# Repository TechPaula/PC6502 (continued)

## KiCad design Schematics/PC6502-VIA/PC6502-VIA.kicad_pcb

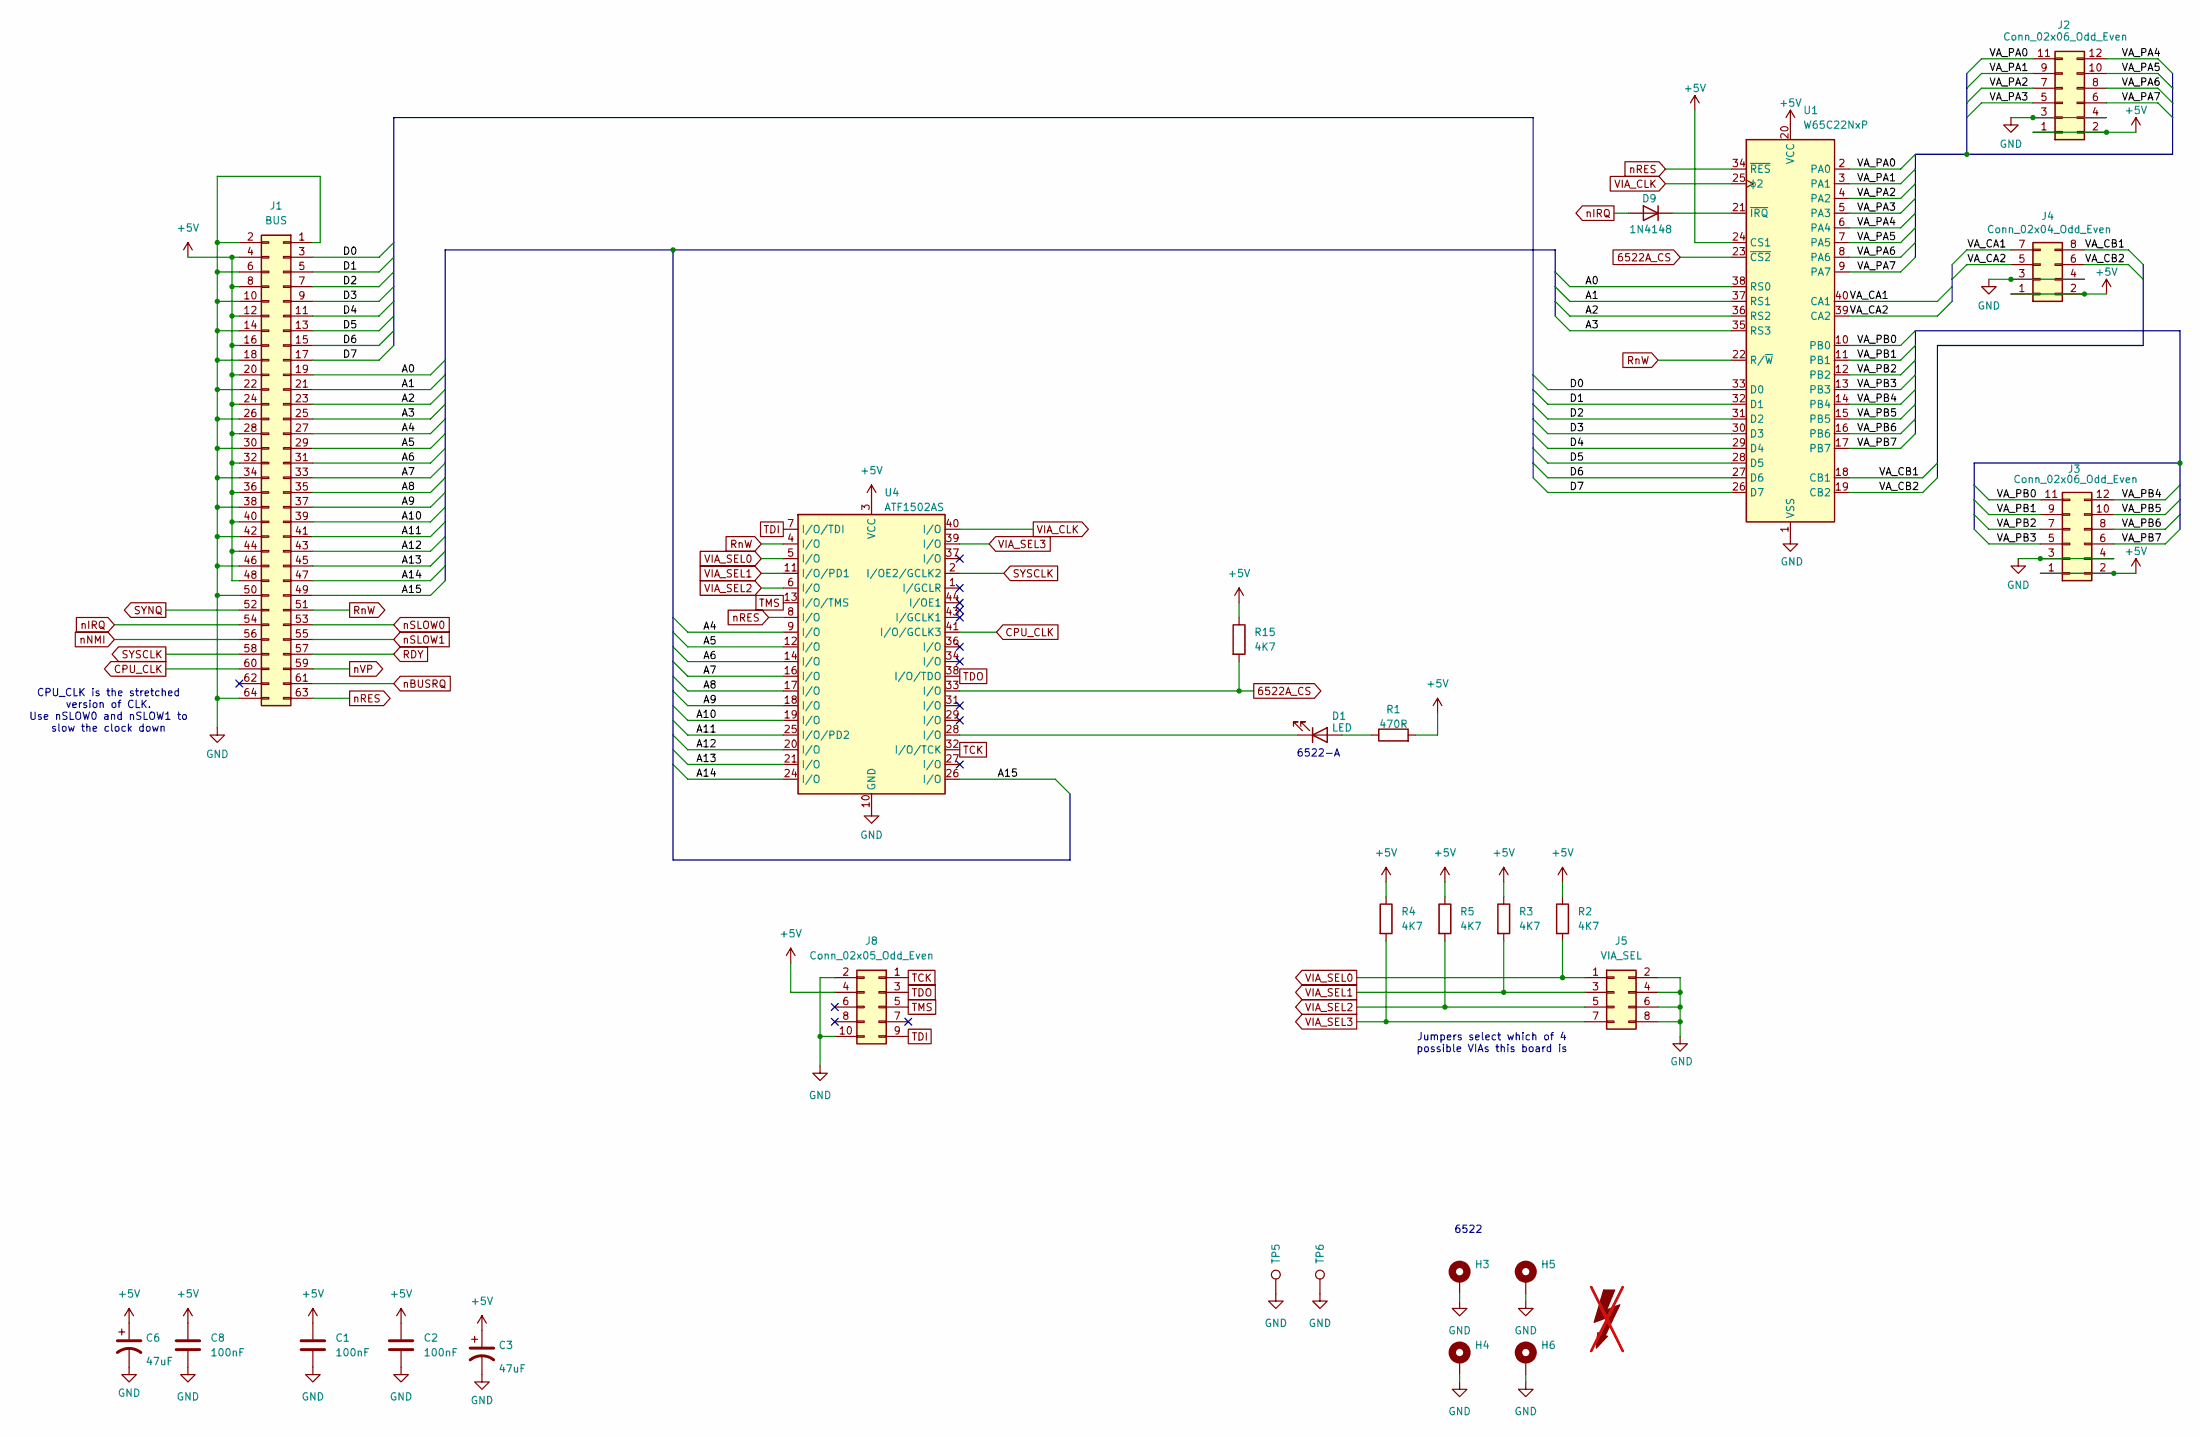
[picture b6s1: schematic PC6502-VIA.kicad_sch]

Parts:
C1, C2, C8: 100nF; C_0805_2012Metric
C3, C6: 47uF; C_1206_3216Metric; LCSC C96123
D1: LED; LTL4221NHBP
D9: 1N4148; D_DO-35_SOD27_P7.62mm_Horizontal
FOX1: SYM_Flash_Large; Fox_avatar_18mm; LCSC DNF; not fitted
H3, H4, H5, H6: MountingHole_Pad; MountingHole_3.2mm_M3_Pad_TopBottom; LCSC DNF
J1: BUS; PinSocket_2x32_P2.54mm_Vertical; LCSC DNF
J2, J3: Conn_02x06_Odd_Even; PinSocket_2x06_P2.54mm_Horizontal
J4: Conn_02x04_Odd_Even; PinSocket_2x04_P2.54mm_Horizontal
J5: VIA_SEL; PinHeader_2x04_P2.54mm_Horizontal
J8: Conn_02x05_Odd_Even; PinHeader_2x05_P2.54mm_Vertical
R1: 470R; R_0603_1608Metric_Pad0.98x0.95mm_HandSolder
R2, R3, R4, R5, R15: 4K7; R_0603_1608Metric_Pad0.98x0.95mm_HandSolder
TP5, TP6: TestPoint; TestPoint_Loop_D1.80mm_Drill1.0mm_Beaded
U1: W65C22NxP; DIP-40_W15.24mm
U4: ATF1502AS; PLCC-44_THT-Socket

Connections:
6522A_CS: R15.2, U1.23 (~CS2), U4.33 (I/O)
+5V: C1.1, C2.1, C3.1, C6.1, C8.1, J1.4, J1.8, J1.12, J1.16, J1.20, J1.24, J1.28, J1.32, J1.36, J1.40, J1.44, J1.48, J2.1, J2.2, J3.1, J3.2, J4.1, J4.2, J8.4, R1.2, R2.1, R3.1, R4.1, R5.1, R15.1, U1.20 (VCC), U1.24 (CS1), U4.3 (VCC), U4.15 (VCC), U4.23 (VCC), U4.35 (VCC)
/A0: J1.19, U1.38 (RS0)
/A1: J1.21, U1.37 (RS1)
/A2: J1.23, U1.36 (RS2)
/A3: J1.25, U1.35 (RS3)
/A4: J1.27, U4.9 (I/O)
/A5: J1.29, U4.12 (I/O)
/A6: J1.31, U4.14 (I/O)
/A7: J1.33, U4.16 (I/O)
/A8: J1.35, U4.17 (I/O)
/A9: J1.37, U4.18 (I/O)
/A10: J1.39, U4.19 (I/O)
/A11: J1.41, U4.25 (I/O/PD2)
/A12: J1.43, U4.20 (I/O)
/A13: J1.45, U4.21 (I/O)
/A14: J1.47, U4.24 (I/O)
/A15: J1.49, U4.26 (I/O)
/D0: J1.3, U1.33 (D0)
/D1: J1.5, U1.32 (D1)
/D2: J1.7, U1.31 (D2)
/D3: J1.9, U1.30 (D3)
/D4: J1.11, U1.29 (D4)
/D5: J1.13, U1.28 (D5)
/D6: J1.15, U1.27 (D6)
/D7: J1.17, U1.26 (D7)
/VA_CA1: J4.7, U1.40 (CA1)
/VA_CA2: J4.5, U1.39 (CA2)
/VA_CB1: J4.8, U1.18 (CB1)
/VA_CB2: J4.6, U1.19 (CB2)
/VA_PA0: J2.11, U1.2 (PA0)
/VA_PA1: J2.9, U1.3 (PA1)
/VA_PA2: J2.7, U1.4 (PA2)
/VA_PA3: J2.5, U1.5 (PA3)
/VA_PA4: J2.12, U1.6 (PA4)
/VA_PA5: J2.10, U1.7 (PA5)
/VA_PA6: J2.8, U1.8 (PA6)
/VA_PA7: J2.6, U1.9 (PA7)
/VA_PB0: J3.11, U1.10 (PB0)
/VA_PB1: J3.9, U1.11 (PB1)
/VA_PB2: J3.7, U1.12 (PB2)
/VA_PB3: J3.5, U1.13 (PB3)
/VA_PB4: J3.12, U1.14 (PB4)
/VA_PB5: J3.10, U1.15 (PB5)
/VA_PB6: J3.8, U1.16 (PB6)
/VA_PB7: J3.6, U1.17 (PB7)
CPU_CLK: J1.60, U4.41 (I/O/GCLK3)
GND: C1.2, C2.2, C3.2, C6.2, C8.2, H3.1, H4.1, H5.1, H6.1, J1.1, J1.2, J1.6, J1.10, J1.14, J1.18, J1.22, J1.26, J1.30, J1.34, J1.38, J1.42, J1.46, J1.50, J1.64, J2.3, J2.4, J3.3, J3.4, J4.3, J4.4, J5.2, J5.4, J5.6, J5.8, J8.2, J8.10, TP5.1, TP6.1, U1.1 (VSS), U4.10 (GND), U4.22 (GND), U4.30 (GND), U4.42 (GND)
unnamed: D1.2 (A), R1.1
unnamed: D1.1 (K), U4.28 (I/O)
unnamed: D9.1 (K), U1.21 (~IRQ)
RDY: J1.57
RnW: J1.51, U1.22 (R/~W), U4.4 (I/O)
SYNQ: J1.52
SYSCLK: J1.58, U4.2 (I/OE2/GCLK2)
TCK: J8.1, U4.32 (I/O/TCK)
TDI: J8.9, U4.7 (I/O/TDI)
TDO: J8.3, U4.38 (I/O/TDO)
TMS: J8.5, U4.13 (I/O/TMS)
VIA_CLK: U1.25 (ϕ2), U4.40 (I/O)
VIA_SEL0: J5.1, R2.2, U4.5 (I/O)
VIA_SEL1: J5.3, R3.2, U4.11 (I/O/PD1)
VIA_SEL2: J5.5, R5.2, U4.6 (I/O)
VIA_SEL3: J5.7, R4.2, U4.39 (I/O)
nBUSRQ: J1.61
nIRQ: D9.2 (A), J1.54
nNMI: J1.56
nRES: J1.63, U1.34 (~RES), U4.8 (I/O)
nSLOW0: J1.53
nSLOW1: J1.55
nVP: J1.59

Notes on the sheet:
6522-A
6522
CPU_CLK is the stretched version of CLK. Use nSLOW0 and nSLOW1 to slow the clock down
Jumpers select which of 4 possible VIAs this board is

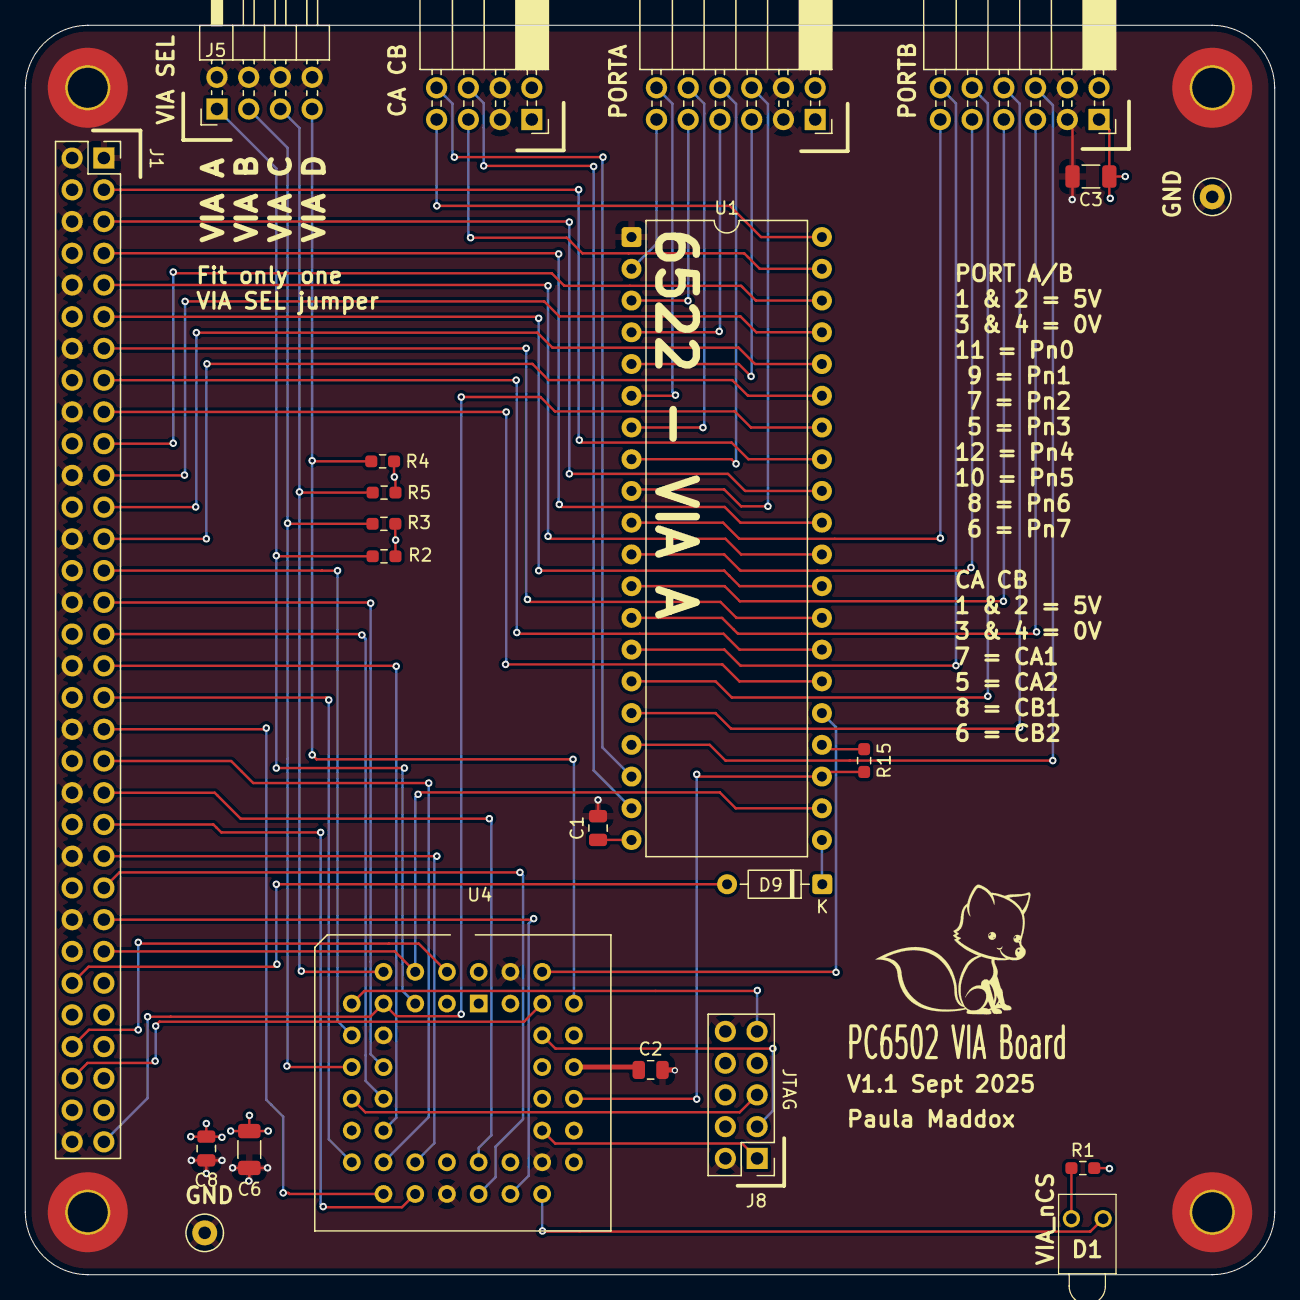
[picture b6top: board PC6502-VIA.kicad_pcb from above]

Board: 4 copper layers, 100.0 x 100.0 mm, 28 parts (0 on the bottom side), 64 nets.

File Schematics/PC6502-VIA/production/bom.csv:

Designator,Footprint,Quantity,Value,LCSC Part #
"C1, C2, C8",0805,3,100nF,
"C3, C6",1206,2,47uF,C96123
D1,LTL4221NHBP,1,LED,
D9,D_DO-35_SOD27_P7.62mm_Horizontal,1,1N4148,
FOX1,Fox_avatar_18mm,1,SYM_Flash_Large,DNF
"H3, H4, H5, H6",MountingHole_3.2mm_M3_Pad_TopBottom,4,MountingHole_Pad,DNF
J1,PinSocket_2x32_P2.54mm_Vertical,1,BUS,DNF
"J2, J3",PinSocket_2x06_P2.54mm_Horizontal,2,Conn_02x06_Odd_Even,
J4,PinSocket_2x04_P2.54mm_Horizontal,1,Conn_02x04_Odd_Even,
J5,PinHeader_2x04_P2.54mm_Horizontal,1,VIA_SEL,
J8,PinHeader_2x05_P2.54mm_Vertical,1,Conn_02x05_Odd_Even,
R1,0603,1,470R,
"R15, R2, R3, R4, R5",0603,5,4K7,
"TP5, TP6",TestPoint_Loop_D1.80mm_Drill1.0mm_Beaded,2,TestPoint,
U1,DIP-40_W15.24mm,1,W65C22NxP,
U4,PLCC-44_THT-Socket,1,ATF1502AS,
